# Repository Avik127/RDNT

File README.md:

# RDNT

RDNT is a project that takes an input audio source and runs signal processing algorithms to drive wired LED strips to create a synchronized audio-visual experience. These audio sources are an onboard analog microphone, an AUX-in port, and a Bluetooth signal from our associated Android app. The user will be able to toggle through the 3 modes, with the microphone being the default, by pressing an external button. This mode toggling will be achieved through a multiplexxed circuit that selects the current mode.
The signal processing algorithms that will be used are the FFT algorithm and a 1-D Gaussian filter. The Gaussian filter reduces noise on the input sample and the FFT algorithm uses this noise reduced signal to isolate frequencies. The LED strips will be driven by a message sender that accepts the output of FFT to create patterns on the wired LED strips.
To create patterns we will send PWM signals to the data pin of the LED strips, these patterns and their associated color ranges can be selected by the user using the associated Android app. The microcontroller will read input samples and compute signal processing algorithms to drive the message sender. The LED strips will be powered by a wall adapter from 120V AC to 5V DC. A switching regulator circuit will drop the 5V DC to 3.3V DC for our microcontroller. For demonstration purposes, we will construct an acrylic display.

See our website for more information: https://engineering.purdue.edu/477grp18/

Current Stage: Soldering components onto our PCB, working on final software, and creating device packaging

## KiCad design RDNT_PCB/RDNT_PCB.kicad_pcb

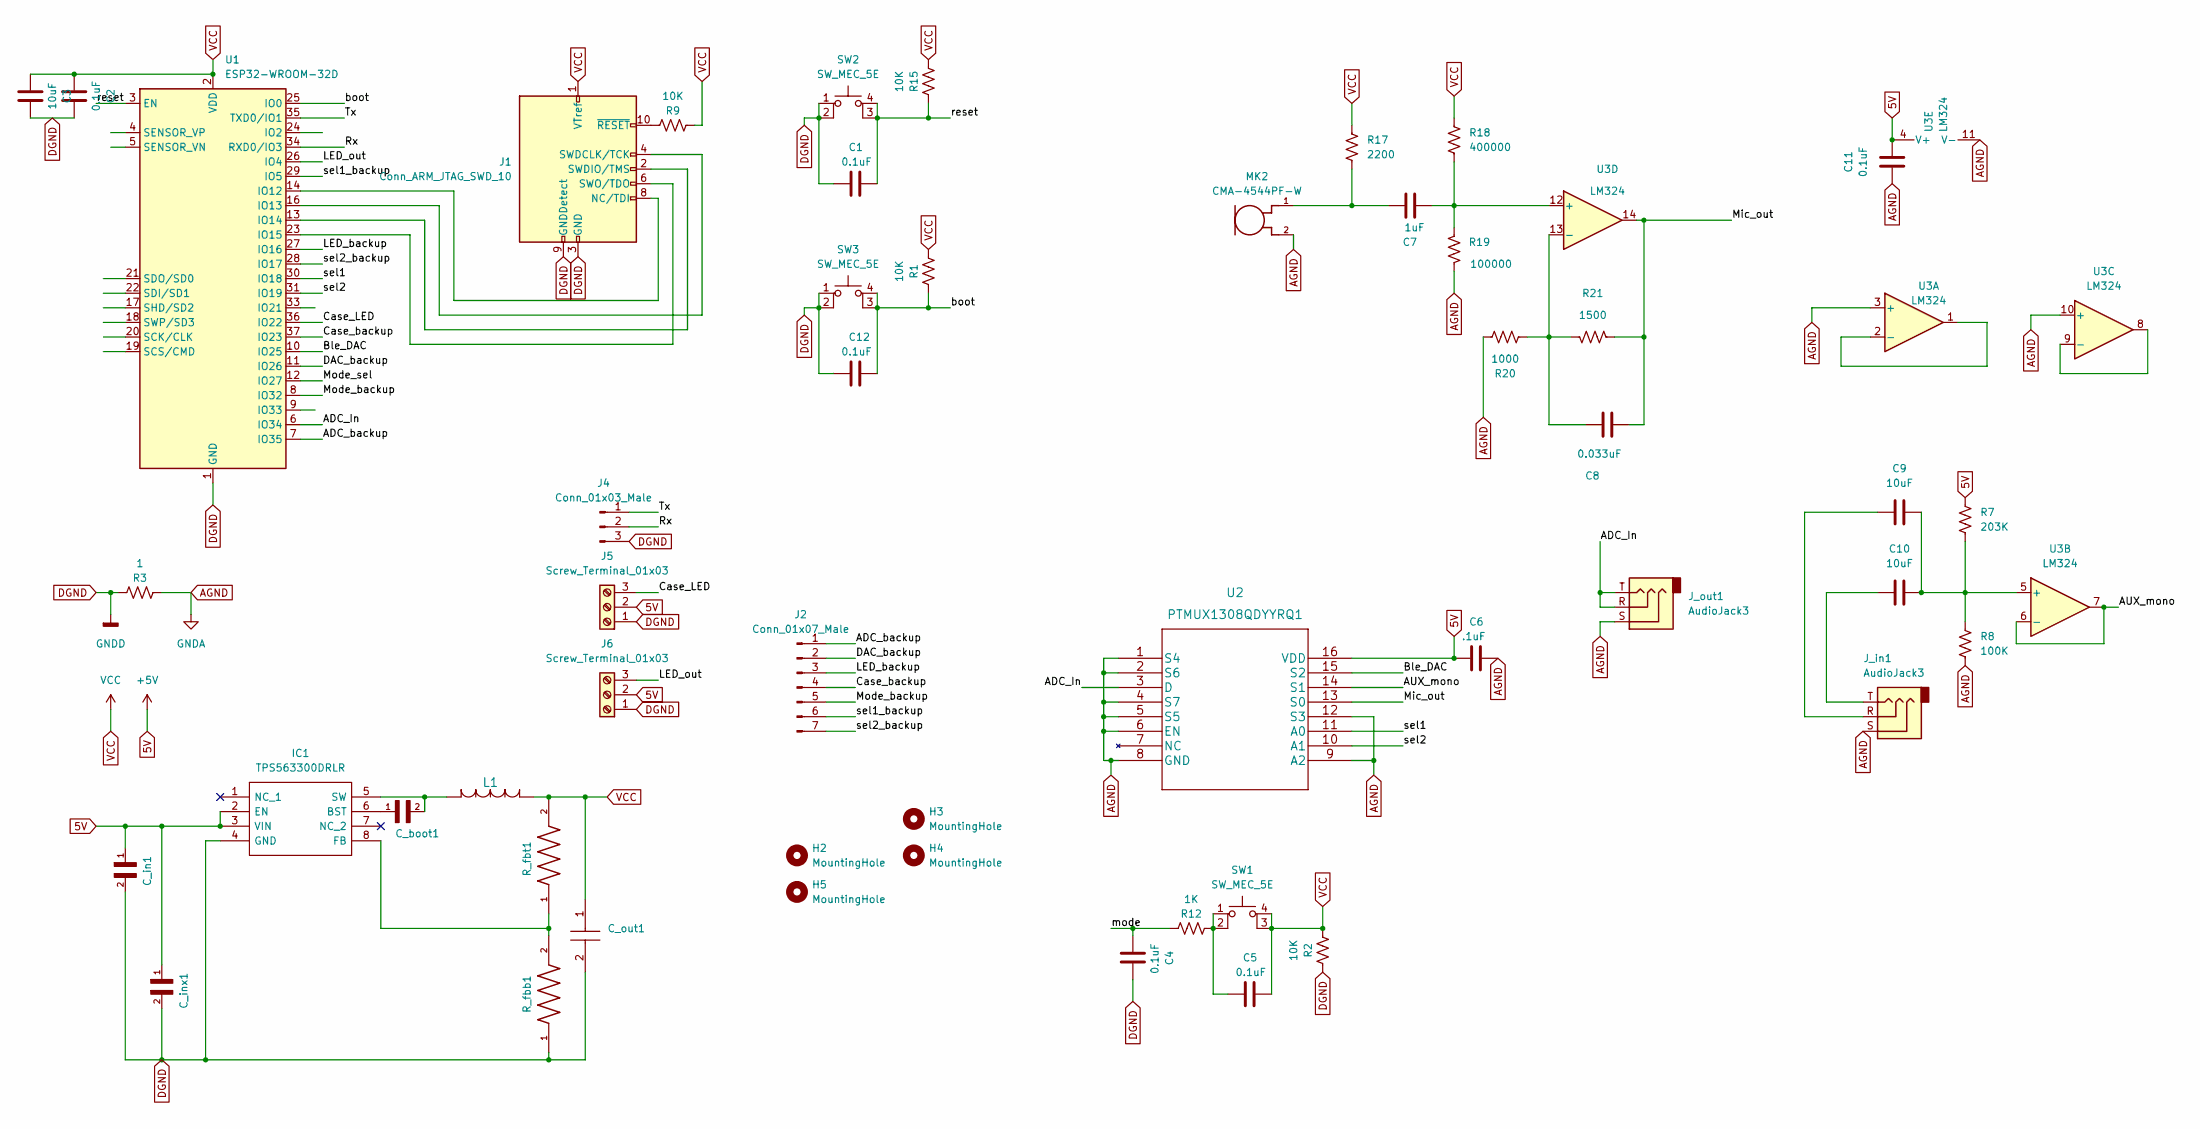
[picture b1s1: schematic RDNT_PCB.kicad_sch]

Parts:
C1, C2, C4, C5, C11, C12: 0.1uF; C_1206_3216Metric
C3, C9, C10: 10uF; C_1206_3216Metric
C6: .1uF; C_1206_3216Metric
C7: 1uF; C_1206_3216Metric
C8: 0.033uF; C_1206_3216Metric
C_boot1: GRM155R71A104KA01D; C_Boot_CAPC1005X55N
C_in1: GRM31CR71E106KA12L; C_IN_CAPC3216X180N
C_inx1: GRM155R71A104KA01D; C_Boot_CAPC1005X55N
C_out1: GRM32EC80J107ME20L; C_OUT_CAPC3225X270N; Mouser Part Number 81-GRM32EC80J107ME0L
H2, H3, H4, H5: MountingHole; MountingHole_3.2mm_M3
IC1: TPS563300DRLR; Mouser Part Number 595-TPS563300DRLR
J1: Conn_ARM_JTAG_SWD_10; PinHeader_2x05_P1.27mm_Vertical_SMD
J2: Conn_01x07_Male
J4: Conn_01x03_Male
J5, J6: Screw_Terminal_01x03; PinHeader_1x03_P2.54mm_Vertical
J_in1: AudioJack3; Jack_3.5mm_CUI_SJ-3523-SMT_Horizontal
J_out1: AudioJack3; Jack_3.5mm_CUI_SJ-3523-SMT_Horizontal
L1: HCM0703-4R7-R; L1_HCM0703-4R7-R
MK2: CMA-4544PF-W; MIC_CMA-4544PF-W
R1, R2, R9, R15: 10K; R_1206_3216Metric
R3: 1; R_1206_3216Metric
R7: 203K; R_1206_3216Metric
R8: 100K; R_1206_3216Metric
R12: 1K; R_1206_3216Metric
R17: 2200; R_1206_3216Metric
R18: 400000; R_1206_3216Metric
R19: 100000; R_1206_3216Metric
R20: 1000; R_1206_3216Metric
R21: 1500; R_1206_3216Metric
R_fbb1: CRCW040210K0FKED; R_FBB_RESC1005X40N
R_fbt1: CRCW060330K9FKEA; R_FBT_RESC1508X50N
SW1, SW2, SW3: SW_MEC_5E; SW_MEC_5GSH9
U1: ESP32-WROOM-32D; ESP32-WROOM-32
U2: PTMUX1308QDYYRQ1
U3: LM324; LM324D

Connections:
5V: C6.2, C11.1, C_in1.1, C_inx1.1, IC1.2 (EN), IC1.3 (VIN), J5.2, J6.2, R7.1, U2.16 (VDD), U3.4 (V+)
/ADC_In: J_out1.R, J_out1.T, U1.6 (IO34), U2.3 (D)
/ADC_backup: J2.1, U1.7 (IO35)
/AUX_mono: U2.14 (S1), U3.6 (-), U3.7
/Ble_DAC: U1.10 (IO25), U2.15 (S2)
/Case_LED: J5.3, U1.36 (IO22)
/Case_backup: J2.4, U1.37 (IO23)
/DAC_backup: J2.2, U1.11 (IO26)
/LED_backup: J2.3, U1.27 (IO16)
/LED_out: J6.3, U1.26 (IO4)
/Mic_out: C8.2, R21.1, U2.13 (S0), U3.14
/Mode_backup: J2.5, U1.8 (IO32)
/Mode_sel: U1.12 (IO27)
/Rx: J4.2, U1.34 (RXD0/IO3)
/Tx: J4.1, U1.35 (TXD0/IO1)
/boot: C12.1, R1.2, SW3.3 (K), SW3.4 (A), U1.25 (IO0)
/mode: C4.2, R12.2
/reset: C1.1, R15.2, SW2.3 (K), SW2.4 (A), U1.3 (EN)
/sel1: U1.30 (IO18), U2.11 (A0)
/sel1_backup: J2.6, U1.29 (IO5)
/sel2: U1.31 (IO19), U2.10 (A1)
/sel2_backup: J2.7, U1.28 (IO17)
AGND: C6.1, C11.2, J_in1.S, J_out1.S, MK2.2, R3.1, R8.2, R19.1, R20.1, U2.1 (S4), U2.2 (S6), U2.4 (S7), U2.5 (S5), U2.6 (EN), U2.8 (GND), U2.9 (A2), U2.12 (S3), U3.3 (+), U3.10 (+), U3.11 (V-)
DGND: C1.2, C2.1, C3.1, C4.1, C12.2, C_in1.2, C_inx1.2, C_out1.2, IC1.4 (GND), J1.3 (GND), J1.5 (GND), J1.9 (GNDDetect), J4.3, J5.1, J6.1, R2.2, R3.2, R_fbb1.1, SW2.1, SW2.2, SW3.1, SW3.2, U1.1 (GND), U1.15 (GND), U1.38 (GND), U1.39 (GND)
unnamed: C5.2, R12.1, SW1.1, SW1.2
unnamed: C7.1, MK2.1, R17.2
unnamed: C7.2, R18.2, R19.2, U3.12 (+)
unnamed: C8.1, R20.2, R21.2, U3.13 (-)
unnamed: C9.2, J_in1.R
unnamed: C9.1, C10.1, R7.2, R8.1, U3.5 (+)
unnamed: C10.2, J_in1.T
unnamed: C_boot1.1, IC1.6 (BST)
unnamed: C_boot1.2, IC1.5 (SW), L1.2
unnamed: IC1.8 (FB), R_fbb1.2, R_fbt1.1
unnamed: J1.2 (SWDIO/TMS), U1.13 (IO14)
unnamed: J1.4 (SWDCLK/TCK), U1.16 (IO13)
unnamed: J1.6 (SWO/TDO), U1.23 (IO15)
unnamed: J1.8 (NC/TDI), U1.14 (IO12)
unnamed: J1.10 (~RESET), R9.2
unnamed: U3.1, U3.2 (-)
unnamed: U3.8, U3.9 (-)
VCC: C2.2, C3.2, C5.1, C_out1.1, J1.1 (VTref), L1.1, R1.1, R2.1, R9.1, R15.1, R17.1, R18.1, R_fbt1.2, SW1.3 (K), SW1.4 (A), U1.2 (VDD)

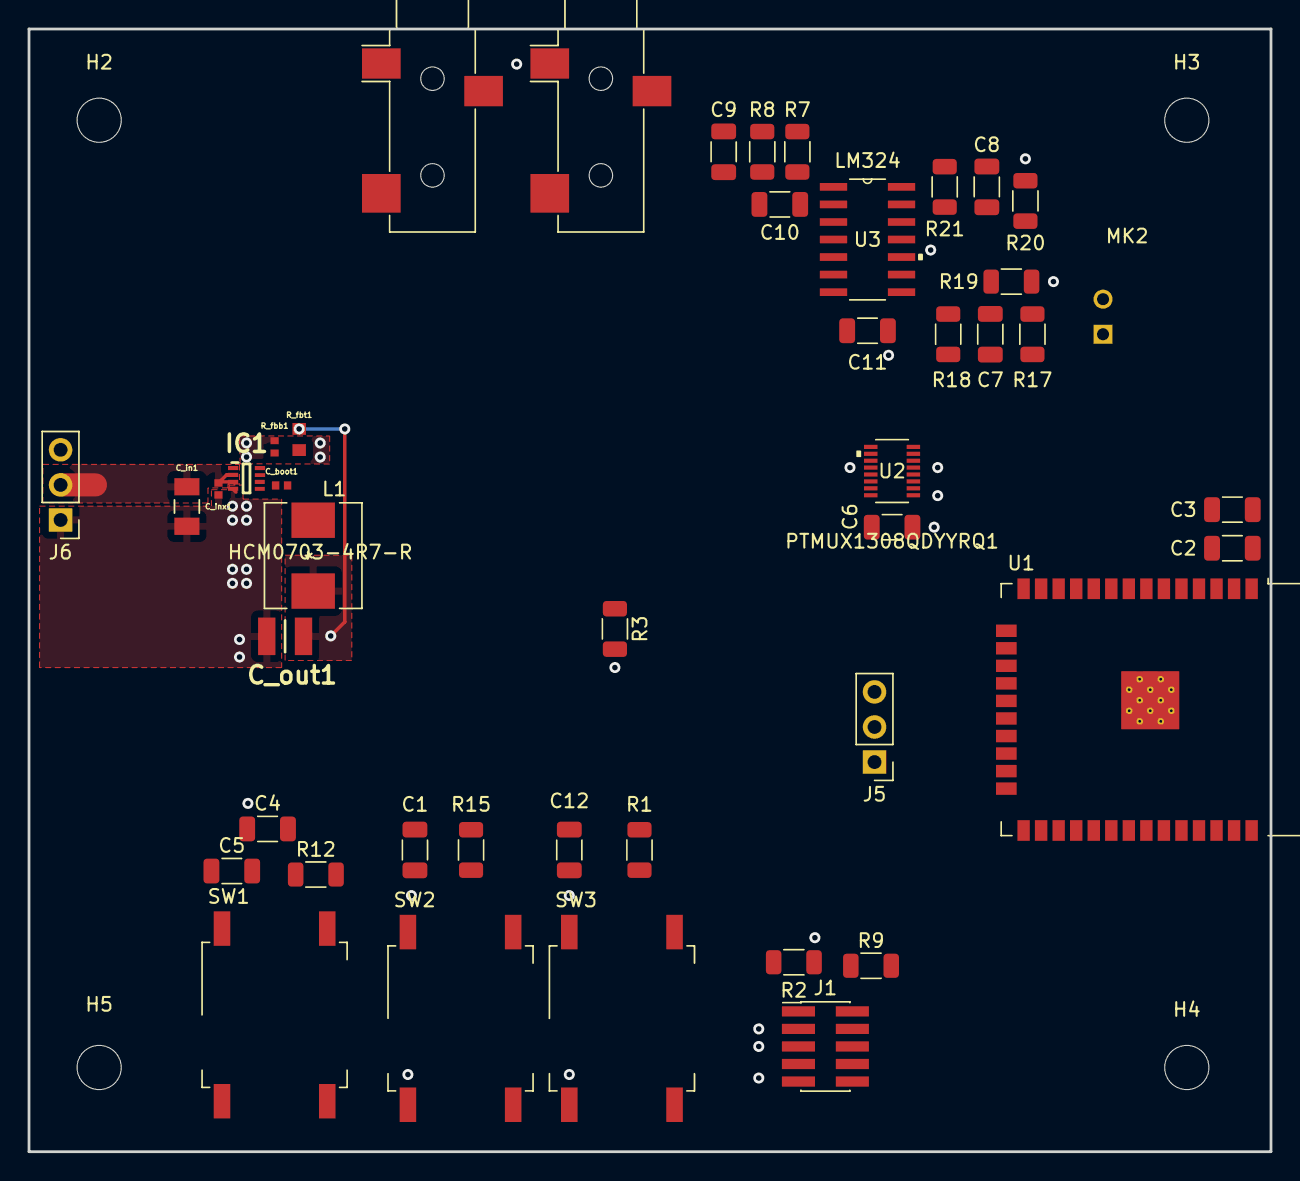
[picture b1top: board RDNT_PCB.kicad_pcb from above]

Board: 2 copper layers, 89.9 x 81.3 mm, 49 parts (1 on the bottom side), 32 nets.

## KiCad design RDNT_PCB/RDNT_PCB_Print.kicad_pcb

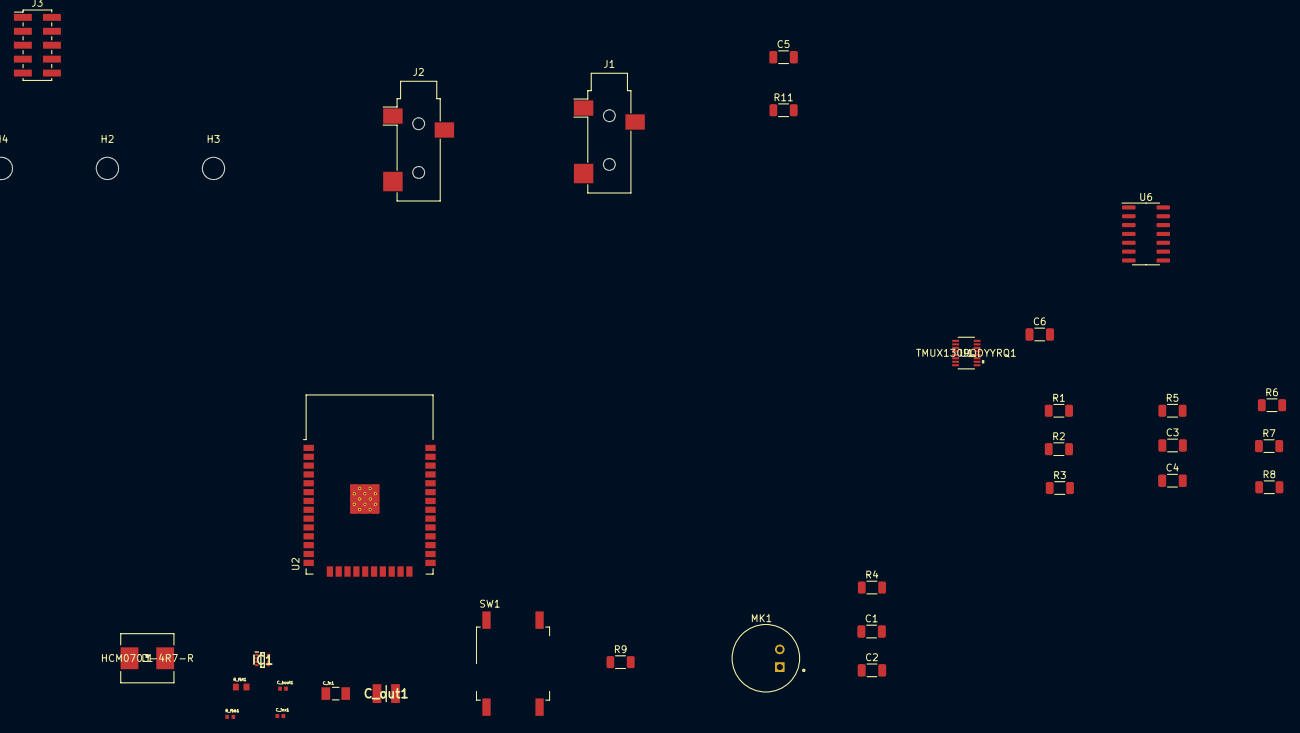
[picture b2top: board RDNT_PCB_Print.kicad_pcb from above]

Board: 2 copper layers, 36 parts (0 on the bottom side), 25 nets, no tracks yet.

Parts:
C1: 1uF; C_1206_3216Metric
C2: 470uF; C_1206_3216Metric
C3, C5: 100uF; C_1206_3216Metric
C4: 10uF; C_1206_3216Metric
C6: .1uF; C_1206_3216Metric
C_boot1: GRM155R71A104KA01D; C_Boot_CAPC1005X55N
C_in1: GRM31CR71E106KA12L; C_IN_CAPC3216X180N
C_inx1: GRM155R71A104KA01D; C_Boot_CAPC1005X55N
C_out1: GRM32EC80J107ME20L; C_OUT_CAPC3225X270N
H1, H2, H3, H4: MountingHole; MountingHole_3.2mm_M3
IC1: TPS563300DRLR
J1, J2: AudioJack3; Jack_3.5mm_CUI_SJ-3523-SMT_Horizontal
J3: Conn_02x05_Counter_Clockwise; PinHeader_2x05_P2.00mm_Vertical_SMD
L1: HCM0703-4R7-R; L1_HCM0703-4R7-R
MK1: CMA-4544PF-W; MIC_CMA-4544PF-W
R1, R3: 100K; R_1206_3216Metric
R2, R5, R9: 1K; R_1206_3216Metric
R4: 22K; R_1206_3216Metric
R6, R11: 330; R_1206_3216Metric
R7: 510; R_1206_3216Metric
R8: 110; R_1206_3216Metric
R_fbb1: CRCW040210K0FKED; R_FBB_RESC1005X40N
R_fbt1: CRCW060330K9FKEA; R_FBT_RESC1508X50N
SW1: SW_MEC_5E; SW_MEC_5GSH9
U1: TMUX1309QDYYRQ1
U2: ESP32-WROOM-32
U6: LM324; SOIC-14_3.9x8.7mm_P1.27mm

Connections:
/+3V3: C2.1, C6.2, C_out1.1, J3.2, L1.1, R4.2, R_fbt1.2, SW1.1, U1.16 (VDD), U2.2 (VDD), U6.4 (V+)
/+5V: C_in1.1, C_inx1.1, IC1.3 (VIN), J3.1
/Audio_Out: J1.R, J1.T, J3.3, U1.3 (D)
/Aux_ADC: C5.1, J3.5, R11.1, U1.15 (S2)
/Ble_ADC: J3.4, U1.12 (S3), U2.6 (IO34)
/Mic_ADC: J3.6, R7.1, R8.1, U1.14 (S1), U6.8
/sel1: J3.8, SW1.4 (A), U1.11 (A0), U2.30 (IO18)
/sel2: J3.7, U1.10 (A1), U2.31 (IO19)
unnamed: C1.1, MK1.2, R4.1
unnamed: C1.2, C2.2, C3.2, MK1.1, R2.1, R3.1, R5.1, R6.2, R8.2
unnamed: C3.1, C4.2, U6.7
unnamed: C4.1, R6.1, U6.10 (+)
unnamed: C5.2, J2.T
unnamed: C_boot1.1, IC1.6 (BST)
unnamed: C_boot1.2, IC1.5 (SW), L1.2
unnamed: C_in1.2, C_inx1.2, C_out1.2, IC1.4 (GND), R_fbb1.1
unnamed: IC1.8 (FB), R_fbb1.2, R_fbt1.1
unnamed: J2.R, J2.S, R11.2
unnamed: R1.1, U6.1
unnamed: R1.2, R2.2, U6.2 (-), U6.6 (-)
unnamed: R3.2, U6.3 (+)
unnamed: R5.2, U6.5 (+)
unnamed: R7.2, U6.9 (-)
unnamed: R9.2, SW1.2
unnamed: U2.1 (GND), U2.15 (GND), U2.38 (GND), U2.39 (GND)

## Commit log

2023-01-11 Check
2023-01-11 Works
2023-01-11 added README
2023-01-11 first web commit. has base tags only
2023-01-11 fixed website folder
2023-01-11 Delete text.txt
    removed test file
2023-01-11 added member1, index and header changes
2023-01-11 updated user page for Graeme Usman
2023-01-12 Done with member details
2023-01-12 added avik profile
2023-01-12 fixed navbar probably
2023-01-12 fixed progress css linking
2023-01-12 fixed progress names and grammar
2023-01-13 {changed}
2023-01-13 changed
2023-01-13 fixed broken contact link
2023-01-13 actually fixed contact link
2023-01-13 Scripts working
2023-01-13 Lets remove your name
2023-01-13 Fixed your name
2023-01-13 added psscs, fixed description
2023-01-17 removed template text on index
2023-01-17 added preliminary PSSCs
2023-01-20 Avik Progress Report Added
2023-01-20 Updated file
2023-01-20 graeme_progress
    Week 1-2 Progress Report for Graeme
2023-01-21 Aviks and Kahaans pr
2023-01-21 anu's progress report weeks 1-2
2023-01-21 Revert "graeme_progress"
    This reverts commit 83d8936e9ce25574f564a555dd4f293010da30b6.
2023-01-21 Revert "Revert "graeme_progress""
    This reverts commit 0515f5e2385677bbc1c00877caab67f209c6ad67.
2023-01-21 Changed img tag for crackerSmasher
2023-01-24 lmao i meant 30 not 50 hours
2023-01-24 okay maybe 30 is still too much :)
2023-01-27 progressReport Done
2023-01-28 added progress reports
2023-01-28 graeme_progress_update
    Week 3 Progress Report: What the dog doing?
2023-01-28 took out joke line
2023-01-28 Week 3 progress report Avik
2023-01-28 Made changed to led and progress
2023-01-28 Made few changes
2023-01-28 avik pr 3
2023-01-28 avik pr 3 update1
2023-01-28 anuraag done ur work
2023-01-31 fixed description and updated PSSCs
2023-01-31 fixed photos
2023-01-31 Change in PSCCs
2023-01-31 Changed the software psccs
2023-01-31 finished lab work for the day
2023-02-02 added wednesday work
2023-02-02 added some thurs work
2023-02-02 addded kicad project
2023-02-02 Updated schematic to current circuitry
2023-02-03 added thurs work after lecture
2023-02-03 forgot hours
2023-02-04 graeme_wk4_progress
2023-02-04 finished up progress report for the week
2023-02-04 fixed formatting. done :)
2023-02-04 Avik Week4 Progress
2023-02-04 Avik Week4 Progress Final
2023-02-07 fft_code
2023-02-08 added tuesdays work
2023-02-08 added FFT+Gaussian+LED program
2023-02-10 PSSCs done
2023-02-10 finished description
2023-02-11 updated progress report and member profile
2023-02-11 graeme progress - week 5
2023-02-11 Avik Week5 PR
2023-02-11 Avik PR5
2023-02-11 Week 5 Changes
2023-02-12 added saturday work
2023-02-13 added face pic
2023-02-13 added my face
    my face
2023-02-13 added resume pdf
2023-02-13 added docs folder to repo
2023-02-14 added documents/refs and fixed formatting on my progress reports
2023-02-14 avik pic added
2023-02-14 Changed PSCC
2023-02-14 Project Done
2023-02-15 added progress
2023-02-17 Added my PR'
2023-02-17 Added my PR
2023-02-18 Graeme Progress
    Week 6 progress report
2023-02-18 added progress for week 6
2023-02-18 fixed date
2023-02-18 Avik PR6
2023-02-19 added espidf fft adc without LED
2023-02-20 added documents. progress report. fixed resume placing
2023-02-21 fixed hours
2023-02-22 updated references after foot print verification day 1
2023-02-22 added tuesday progress report
2023-02-23 added wednesday progress
2023-02-25 graeme week7 progress
2023-02-25 Avik PR7
2023-02-25 Submitted my report
2023-02-27 changed slideshow
2023-02-27 fixed team at work photo
2023-02-27 added github readme
2023-02-27 fixed grammar in desc/PSSCs. updated A0 and A1
2023-02-28 added led strip datasheet
2023-03-02 website updated pcb and presentation
2023-03-02 team presentation updated
2023-03-02 CAD updated
2023-03-02 presentation up
2023-03-04 updated software folder and added descriptive names
2023-03-10 Progress report completed
2023-03-10 I hope its right
2023-03-10 added week8/9 progress report
2023-03-10 graeme_progress
    Week 8-9 Progress Update
2023-03-11 Avik PR9
2023-03-11 Avik PR 9 Pic Size edited
2023-03-13 PCB Updated
2023-03-14 zipped grb drl
2023-03-21 pushed pcb on website
2023-03-21 Drill Files Uploaded
2023-03-21 updated file struct
2023-03-24 graeme_progress
    Week 10 Progress Report
2023-03-24 added anu progress report
2023-03-25 Avik PR11
2023-03-25 Completed report
2023-03-25 picture issue fixed PR10 Avik
2023-03-28 added prototyping folder. added first test file
2023-03-30 got PWM working for black/white control. added file for testing the pcb
2023-03-31 added anu progress wk11
2023-04-01 done with progress report
2023-04-04 added led driving prototype file
2023-04-05 added tuesday progres
2023-04-05 added a test file for mode switch
2023-04-05 fixed formatting
2023-04-05 added test file for mode button and caseled
2023-04-06 fixed small bugs on verification files
2023-04-06 fixed mode button :D
2023-04-06 added caseled, still not done
2023-04-07 graeme_progres
    Week 12 Progress Report
2023-04-07 Avik PR13 Done
2023-04-08 Added progress reprot
2023-04-08 Created a workflow for no interruption
2023-04-08 actually added pr my b last time
2023-04-14 fixed debouncing on modebutton/case_led
2023-04-14 ESP_ITER1
    With ADC , Bluetooth
2023-04-14 better mode switching, changes muxx outputs now as well
2023-04-15 graeme progress
    Week 13 Progress Report
2023-04-15 added anu pr
2023-04-15 added some photos
2023-04-15 Avik PR14
2023-04-15 Progress report up
2023-04-15 Changes in progress report
2023-04-15 Changes in Image
2023-04-15 Changed Image dimensions
2023-04-15 Few more changes
2023-04-15 added first_try pssc 5/2
2023-04-15 small change to fix loops/vars
2023-04-18 finished PSSC 5 with code added
2023-04-19 added LED encoder files
2023-04-20 added code that works for 3. needs app to drive it
2023-04-20 fixed file names
2023-04-20 my bad forgot to actually add program
2023-04-21 mostly full code done
2023-04-21 added dc signal input to fft example
2023-04-21 added fft for ac signal
2023-04-21 Changed Pssc's
2023-04-21 fixed name
2023-04-21 fixed dc voltage scaling for gaussian
2023-04-21 added final progress report
2023-04-21 changed photo and about page
2023-04-21 graeme progress
    week 14 progress report
2023-04-21 Pushed Progress Report
2023-04-22 fixed slightly :)
2023-04-22 Avik PR15
2023-04-25 Team Block Diagram FInal
2023-04-26 added Kahaan's app
2023-04-26 added final software

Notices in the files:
parts and their libraries:
Copyright 2021 Accelerated Designs. All rights reserved.
